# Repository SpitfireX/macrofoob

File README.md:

# macrofoob
A QMK-powered 5x5 macro pad with hot swap sockets and RGB underglow

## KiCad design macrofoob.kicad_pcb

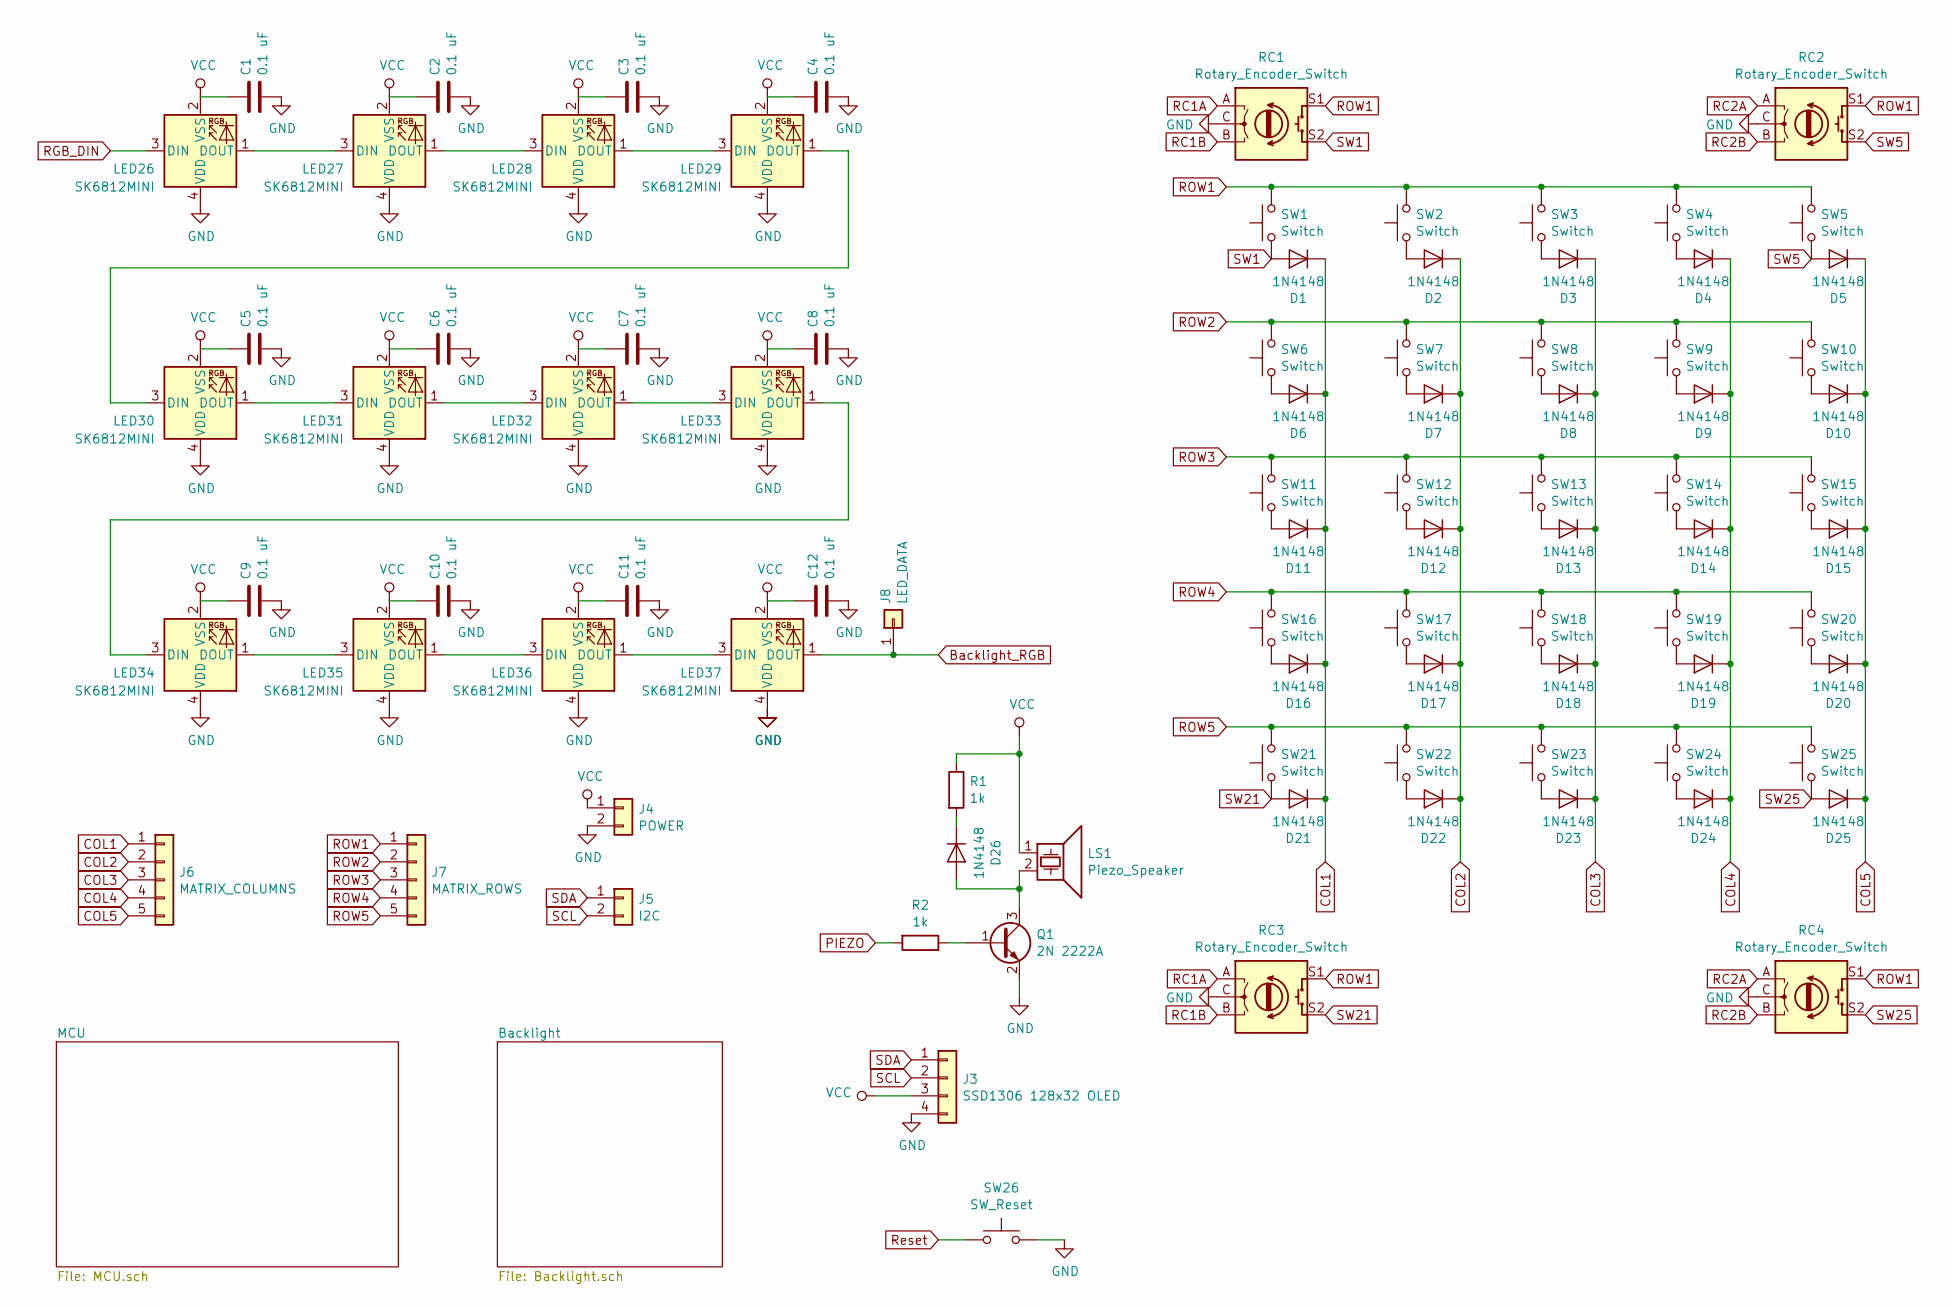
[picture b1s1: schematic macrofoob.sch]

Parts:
C1, C2, C3, C4, C5, C6, C7, C8, C9, C10, C11, C12: 0.1 uF; C_0805_2012Metric
D1, D2, D3, D4, D5, D6, D7, D8, D9, D10, D11, D12, D13, D14, D15, D16, D17, D18, D19, D20, D21, D22, D23, D24, D25, D26: 1N4148; D_MiniMELF
J3: SSD1306 128x32 OLED; PinHeader_1x04_P2.54mm_Vertical
J4: POWER; Generic_Pads_2mm_1x2
J5: I2C; Generic_Pads_2mm_1x2
J6: MATRIX_COLUMNS; Generic_Pads_2mm_1x5
J7: MATRIX_ROWS; Generic_Pads_2mm_1x5
J8: LED_DATA; Generic_Pads_2mm_1x1
LED26, LED27, LED28, LED29, LED30, LED31, LED32, LED33, LED34, LED35, LED36, LED37: SK6812MINI; LED_SK6812MINI_PLCC4_3.5x3.5mm_P1.75mm
LS1: Piezo_Speaker; PinHeader_1x02_P2.54mm_Vertical
Q1: 2N 2222A; SOT-23
R1, R2: 1k; R_0805_2012Metric
RC1, RC2, RC3, RC4: Rotary_Encoder_Switch; RotaryEncoder_Alps_EC11E-Switch_Vertical_H20mm_custom
SW1, SW2, SW3, SW4, SW5, SW6, SW7, SW8, SW9, SW10, SW11, SW12, SW13, SW14, SW15, SW16, SW17, SW18, SW19, SW20, SW21, SW22, SW23, SW24, SW25: Switch; Kailh_socket_optional
SW26: SW_Reset; SW_SPST_PTS810

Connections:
Backlight_RGB: J8.1, LED37.1 (DOUT); also elsewhere on the board
COL1: D1.1 (K), D6.1 (K), D11.1 (K), D16.1 (K), D21.1 (K), J6.1; also elsewhere on the board
COL2: D2.1 (K), D7.1 (K), D12.1 (K), D17.1 (K), D22.1 (K), J6.2; also elsewhere on the board
COL3: D3.1 (K), D8.1 (K), D13.1 (K), D18.1 (K), D23.1 (K), J6.3; also elsewhere on the board
COL4: D4.1 (K), D9.1 (K), D14.1 (K), D19.1 (K), D24.1 (K), J6.4; also elsewhere on the board
COL5: D5.1 (K), D10.1 (K), D15.1 (K), D20.1 (K), D25.1 (K), J6.5; also elsewhere on the board
GND: C1.2, C2.2, C3.2, C4.2, C5.2, C6.2, C7.2, C8.2, C9.2, C10.2, C11.2, C12.2, J3.4, J4.2, LED26.4 (VDD), LED27.4 (VDD), LED28.4 (VDD), LED29.4 (VDD), LED30.4 (VDD), LED31.4 (VDD), LED32.4 (VDD), LED33.4 (VDD), LED34.4 (VDD), LED35.4 (VDD), LED36.4 (VDD), LED37.4 (VDD), Q1.2 (E), RC1.C, RC2.C, RC3.C, RC4.C, SW26.2; also elsewhere on the board
unnamed: D2.2 (A), SW2.1
unnamed: D3.2 (A), SW3.1
unnamed: D4.2 (A), SW4.1
unnamed: D6.2 (A), SW6.1
unnamed: D7.2 (A), SW7.1
unnamed: D8.2 (A), SW8.1
unnamed: D9.2 (A), SW9.1
unnamed: D10.2 (A), SW10.1
unnamed: D11.2 (A), SW11.1
unnamed: D12.2 (A), SW12.1
unnamed: D13.2 (A), SW13.1
unnamed: D14.2 (A), SW14.1
unnamed: D15.2 (A), SW15.1
unnamed: D16.2 (A), SW16.1
unnamed: D17.2 (A), SW17.1
unnamed: D18.2 (A), SW18.1
unnamed: D19.2 (A), SW19.1
unnamed: D20.2 (A), SW20.1
unnamed: D22.2 (A), SW22.1
unnamed: D23.2 (A), SW23.1
unnamed: D24.2 (A), SW24.1
unnamed: D26.1 (K), R1.2
unnamed: D26.2 (A), LS1.2, Q1.3 (C)
unnamed: LED26.1 (DOUT), LED27.3 (DIN)
unnamed: LED27.1 (DOUT), LED28.3 (DIN)
unnamed: LED28.1 (DOUT), LED29.3 (DIN)
unnamed: LED29.1 (DOUT), LED30.3 (DIN)
unnamed: LED30.1 (DOUT), LED31.3 (DIN)
unnamed: LED31.1 (DOUT), LED32.3 (DIN)
unnamed: LED32.1 (DOUT), LED33.3 (DIN)
unnamed: LED33.1 (DOUT), LED34.3 (DIN)
unnamed: LED34.1 (DOUT), LED35.3 (DIN)
unnamed: LED35.1 (DOUT), LED36.3 (DIN)
unnamed: LED36.1 (DOUT), LED37.3 (DIN)
unnamed: Q1.1 (B), R2.1
PIEZO: R2.2; also elsewhere on the board
RC1A: RC1.A, RC3.A; also elsewhere on the board
RC1B: RC1.B, RC3.B; also elsewhere on the board
RC2A: RC2.A, RC4.A; also elsewhere on the board
RC2B: RC2.B, RC4.B; also elsewhere on the board
RGB_DIN: LED26.3 (DIN); also elsewhere on the board
ROW1: J7.1, RC1.S1, RC2.S1, RC3.S1, RC4.S1, SW1.2, SW2.2, SW3.2, SW4.2, SW5.2; also elsewhere on the board
ROW2: J7.2, SW6.2, SW7.2, SW8.2, SW9.2, SW10.2; also elsewhere on the board
ROW3: J7.3, SW11.2, SW12.2, SW13.2, SW14.2, SW15.2; also elsewhere on the board
ROW4: J7.4, SW16.2, SW17.2, SW18.2, SW19.2, SW20.2; also elsewhere on the board
ROW5: J7.5, SW21.2, SW22.2, SW23.2, SW24.2, SW25.2; also elsewhere on the board
Reset: SW26.1; also elsewhere on the board
SCL: J3.2, J5.2; also elsewhere on the board
SDA: J3.1, J5.1; also elsewhere on the board
SW1: D1.2 (A), RC1.S2, SW1.1
SW5: D5.2 (A), RC2.S2, SW5.1
SW21: D21.2 (A), RC3.S2, SW21.1
SW25: D25.2 (A), RC4.S2, SW25.1
VCC: C1.1, C2.1, C3.1, C4.1, C5.1, C6.1, C7.1, C8.1, C9.1, C10.1, C11.1, C12.1, J3.3, J4.1, LED26.2 (VSS), LED27.2 (VSS), LED28.2 (VSS), LED29.2 (VSS), LED30.2 (VSS), LED31.2 (VSS), LED32.2 (VSS), LED33.2 (VSS), LED34.2 (VSS), LED35.2 (VSS), LED36.2 (VSS), LED37.2 (VSS), LS1.1, R1.1; also elsewhere on the board

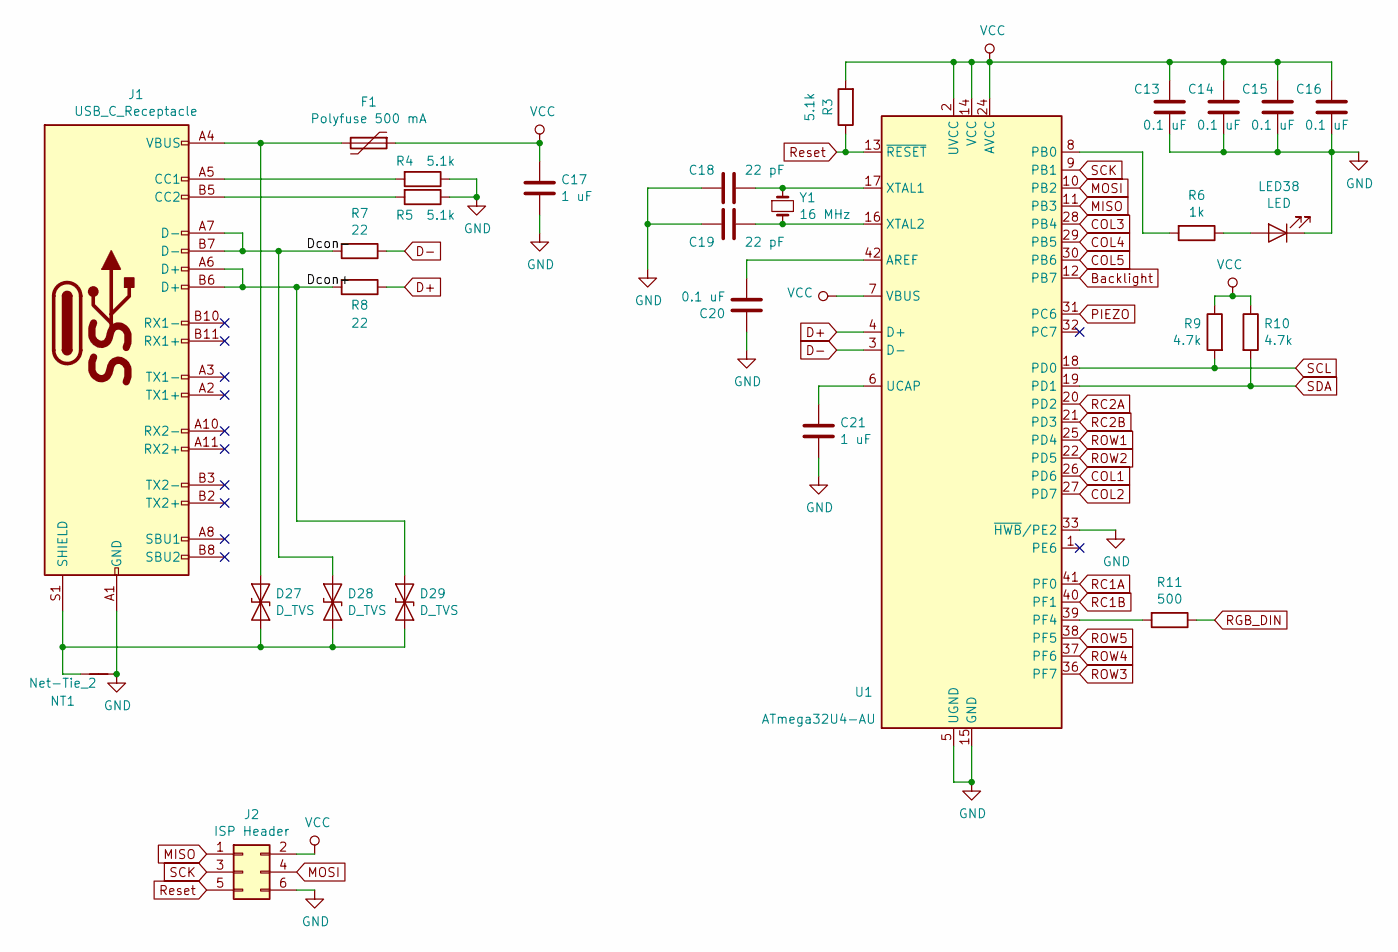
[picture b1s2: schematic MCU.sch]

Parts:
C13, C14, C15, C16, C20: 0.1 uF; C_0805_2012Metric
C17, C21: 1 uF; C_0805_2012Metric
C18, C19: 22 pF; C_0805_2012Metric
D27, D28, D29: D_TVS; D_SMA
F1: Polyfuse 500 mA; Fuse_1812_4532Metric
J1: USB_C_Receptacle; HRO-TYPE-C-31-M-12_kicad-pinout
J2: ISP Header; PinHeader_2x03_P2.54mm_Vertical
LED38: LED; LED_0805_2012Metric
NT1: Net-Tie_2; NetTie-2_SMD_Pad2.0mm
R3, R4, R5: 5.1k; R_0805_2012Metric
R6: 1k; R_0805_2012Metric
R7, R8: 22; R_0805_2012Metric
R9, R10: 4.7k; R_0805_2012Metric
R11: 500; R_0805_2012Metric
U1: ATmega32U4-AU; TQFP-44_10x10mm_P0.8mm
Y1: 16 MHz; R_1210_3225Metric

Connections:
/MCU/Dcon+: D29.1 (A1), J1.A6 (D+), J1.B6 (D+), R8.2
/MCU/Dcon-: D28.1 (A1), J1.A7 (D-), J1.B7 (D-), R7.2
Backlight: U1.12 (PB7); also elsewhere on the board
COL1: U1.26 (PD6); also elsewhere on the board
COL2: U1.27 (PD7); also elsewhere on the board
COL3: U1.28 (PB4); also elsewhere on the board
COL4: U1.29 (PB5); also elsewhere on the board
COL5: U1.30 (PB6); also elsewhere on the board
D+: R8.1, U1.4 (D+)
D-: R7.1, U1.3 (D-)
GND: C13.1, C14.1, C15.1, C16.1, C17.2, C18.2, C19.2, C20.1, C21.2, J1.A1 (GND), J1.A12 (GND), J1.B1 (GND), J1.B12 (GND), J2.6, LED38.1 (K), NT1.2, R4.1, R5.1, U1.5 (UGND), U1.15 (GND), U1.23 (GND), U1.33 (~HWB~/PE2), U1.35 (GND), U1.43 (GND); also elsewhere on the board
MISO: J2.1, U1.11 (PB3)
MOSI: J2.4, U1.10 (PB2)
unnamed: C18.1, U1.17 (XTAL1), Y1.1
unnamed: C19.1, U1.16 (XTAL2), Y1.2
unnamed: C20.2, U1.42 (AREF)
unnamed: C21.1, U1.6 (UCAP)
unnamed: D27.1 (A1), F1.2, J1.A4 (VBUS), J1.A9 (VBUS), J1.B4 (VBUS), J1.B9 (VBUS)
unnamed: D27.2 (A2), D28.2 (A2), D29.2 (A2), J1.S1 (SHIELD), NT1.1
unnamed: J1.A5 (CC1), R4.2
unnamed: J1.B5 (CC2), R5.2
unnamed: LED38.2 (A), R6.1
unnamed: R6.2, U1.8 (PB0)
unnamed: R11.2, U1.39 (PF4)
PIEZO: U1.31 (PC6); also elsewhere on the board
RC1A: U1.41 (PF0); also elsewhere on the board
RC1B: U1.40 (PF1); also elsewhere on the board
RC2A: U1.20 (PD2); also elsewhere on the board
RC2B: U1.21 (PD3); also elsewhere on the board
RGB_DIN: R11.1; also elsewhere on the board
ROW1: U1.25 (PD4); also elsewhere on the board
ROW2: U1.22 (PD5); also elsewhere on the board
ROW3: U1.36 (PF7); also elsewhere on the board
ROW4: U1.37 (PF6); also elsewhere on the board
ROW5: U1.38 (PF5); also elsewhere on the board
Reset: J2.5, R3.1, U1.13 (~RESET); also elsewhere on the board
SCK: J2.3, U1.9 (PB1)
SCL: R9.2, U1.18 (PD0); also elsewhere on the board
SDA: R10.2, U1.19 (PD1); also elsewhere on the board
VCC: C13.2, C14.2, C15.2, C16.2, C17.1, F1.1, J2.2, R3.2, R9.1, R10.1, U1.2 (UVCC), U1.7 (VBUS), U1.14 (VCC), U1.24 (AVCC), U1.34 (VCC), U1.44 (AVCC); also elsewhere on the board

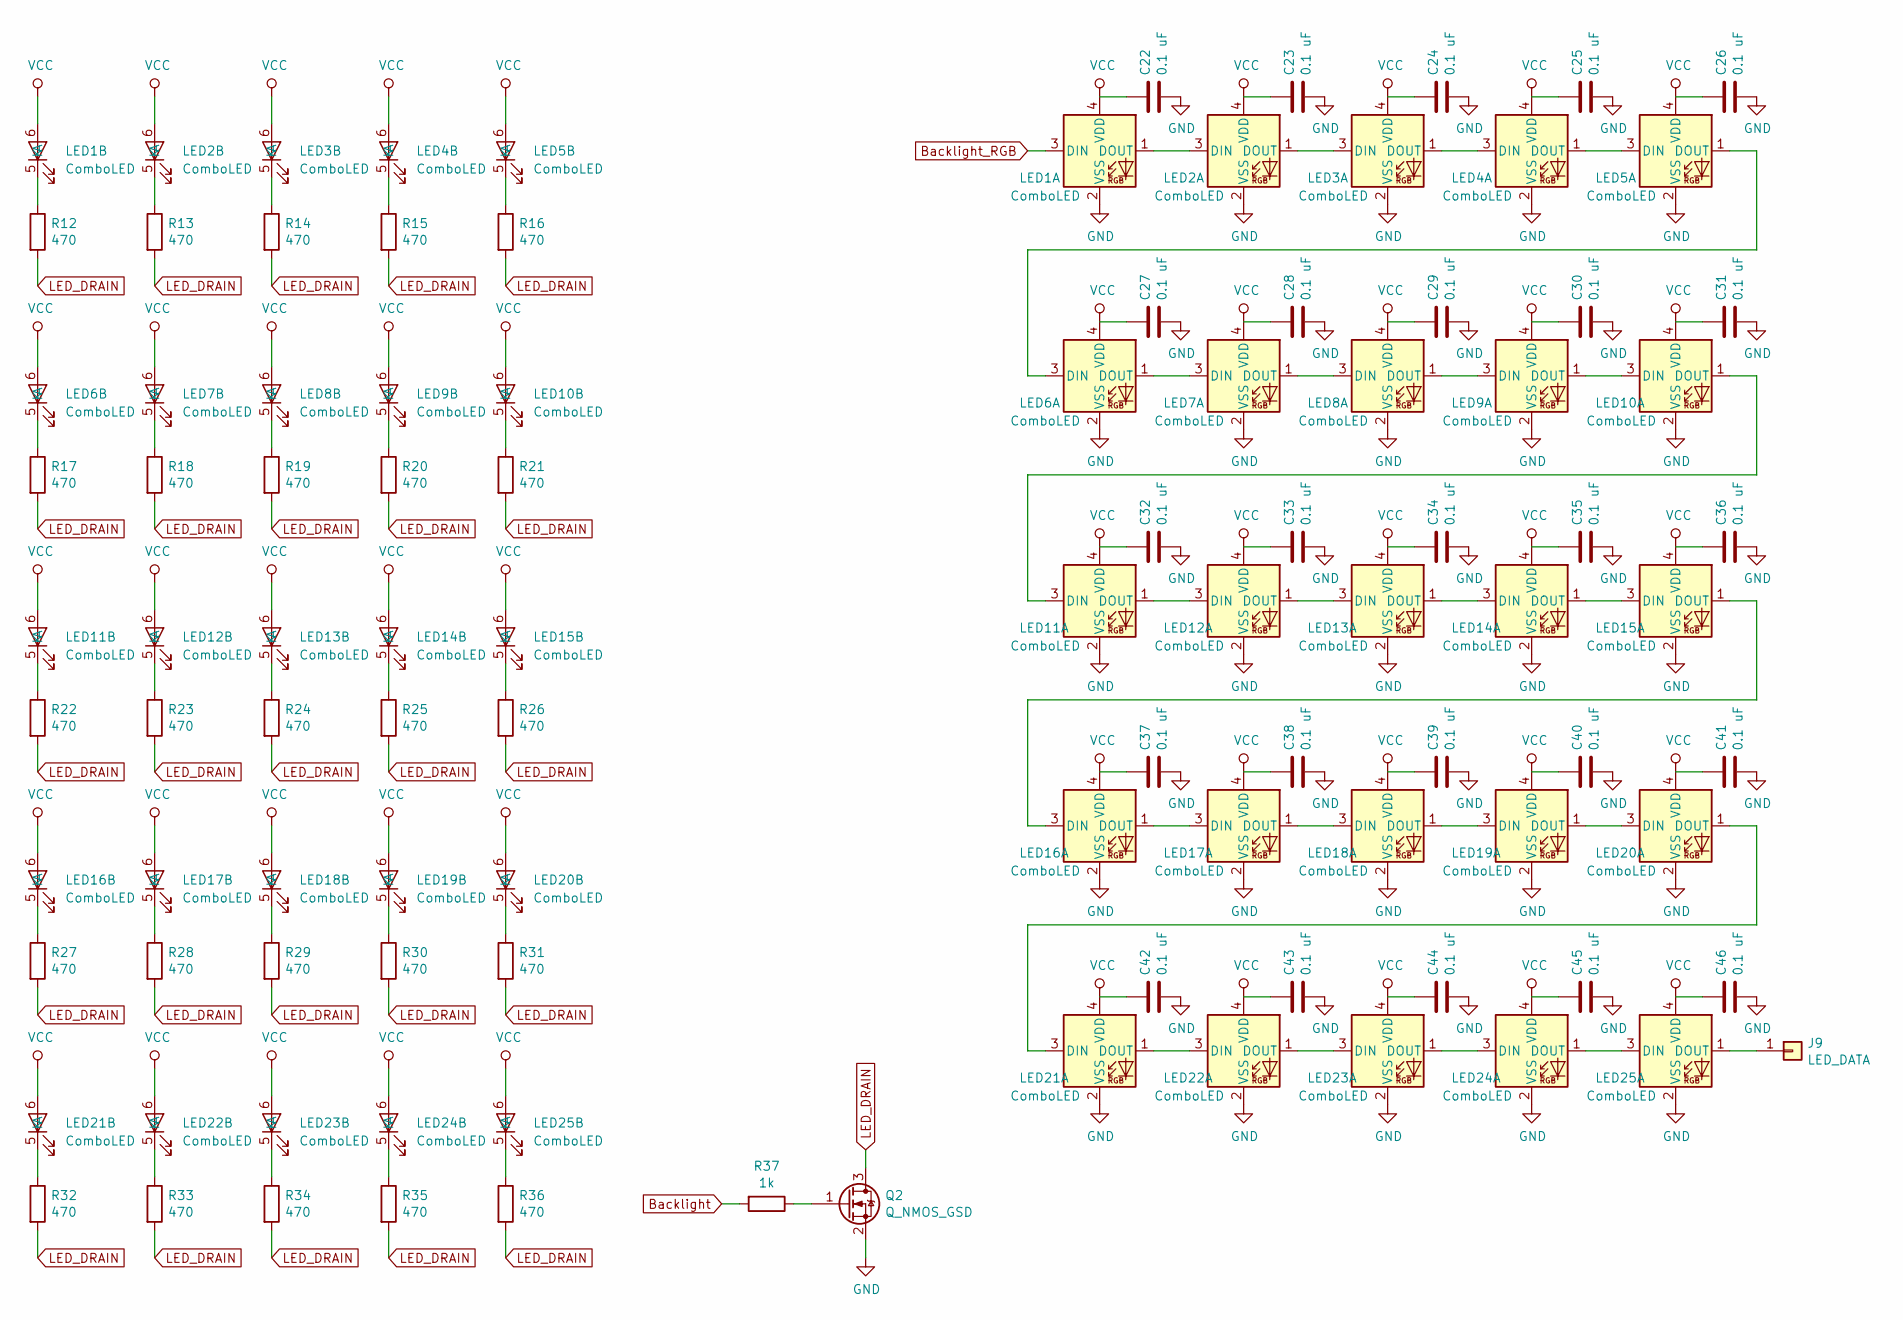
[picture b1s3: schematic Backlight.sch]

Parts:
C22, C23, C24, C25, C26, C27, C28, C29, C30, C31, C32, C33, C34, C35, C36, C37, C38, C39, C40, C41, C42, C43, C44, C45, C46: 0.1 uF; C_0805_2012Metric
J9: LED_DATA; Generic_Pads_2mm_1x1
LED1, LED2, LED3, LED4, LED5, LED6, LED7, LED8, LED9, LED10, LED11, LED12, LED13, LED14, LED15, LED16, LED17, LED18, LED19, LED20, LED21, LED22, LED23, LED24, LED25: ComboLED; LED_combined_SK6812MINI_0805
Q2: Q_NMOS_GSD; SOT-23
R12, R13, R14, R15, R16, R17, R18, R19, R20, R21, R22, R23, R24, R25, R26, R27, R28, R29, R30, R31, R32, R33, R34, R35, R36: 470; R_0805_2012Metric
R37: 1k; R_0805_2012Metric

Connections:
Backlight: R37.2; also elsewhere on the board
Backlight_RGB: LED1.3 (DIN); also elsewhere on the board
GND: C22.2, C23.2, C24.2, C25.2, C26.2, C27.2, C28.2, C29.2, C30.2, C31.2, C32.2, C33.2, C34.2, C35.2, C36.2, C37.2, C38.2, C39.2, C40.2, C41.2, C42.2, C43.2, C44.2, C45.2, C46.2, LED1.2 (VSS), LED2.2 (VSS), LED3.2 (VSS), LED4.2 (VSS), LED5.2 (VSS), LED6.2 (VSS), LED7.2 (VSS), LED8.2 (VSS), LED9.2 (VSS), LED10.2 (VSS), LED11.2 (VSS), LED12.2 (VSS), LED13.2 (VSS), LED14.2 (VSS), LED15.2 (VSS), LED16.2 (VSS), LED17.2 (VSS), LED18.2 (VSS), LED19.2 (VSS), LED20.2 (VSS), LED21.2 (VSS), LED22.2 (VSS), LED23.2 (VSS), LED24.2 (VSS), LED25.2 (VSS), Q2.2 (S); also elsewhere on the board
LED_DRAIN: Q2.3 (D), R12.2, R13.2, R14.2, R15.2, R16.2, R17.2, R18.2, R19.2, R20.2, R21.2, R22.2, R23.2, R24.2, R25.2, R26.2, R27.2, R28.2, R29.2, R30.2, R31.2, R32.2, R33.2, R34.2, R35.2, R36.2
unnamed: J9.1, LED25.1 (DOUT)
unnamed: LED1.1 (DOUT), LED2.3 (DIN)
unnamed: LED1.5 (K), R12.1
unnamed: LED2.1 (DOUT), LED3.3 (DIN)
unnamed: LED2.5 (K), R13.1
unnamed: LED3.1 (DOUT), LED4.3 (DIN)
unnamed: LED3.5 (K), R14.1
unnamed: LED4.1 (DOUT), LED5.3 (DIN)
unnamed: LED4.5 (K), R15.1
unnamed: LED5.1 (DOUT), LED6.3 (DIN)
unnamed: LED5.5 (K), R16.1
unnamed: LED6.1 (DOUT), LED7.3 (DIN)
unnamed: LED6.5 (K), R17.1
unnamed: LED7.1 (DOUT), LED8.3 (DIN)
unnamed: LED7.5 (K), R18.1
unnamed: LED8.1 (DOUT), LED9.3 (DIN)
unnamed: LED8.5 (K), R19.1
unnamed: LED9.5 (K), R20.1
unnamed: LED10.1 (DOUT), LED11.3 (DIN)
unnamed: LED9.1 (DOUT), LED10.3 (DIN)
unnamed: LED10.5 (K), R21.1
unnamed: LED11.1 (DOUT), LED12.3 (DIN)
unnamed: LED11.5 (K), R22.1
unnamed: LED12.1 (DOUT), LED13.3 (DIN)
unnamed: LED12.5 (K), R23.1
unnamed: LED13.1 (DOUT), LED14.3 (DIN)
unnamed: LED13.5 (K), R24.1
unnamed: LED14.1 (DOUT), LED15.3 (DIN)
unnamed: LED14.5 (K), R25.1
unnamed: LED15.1 (DOUT), LED16.3 (DIN)
unnamed: LED15.5 (K), R26.1
unnamed: LED16.1 (DOUT), LED17.3 (DIN)
unnamed: LED16.5 (K), R27.1
unnamed: LED17.1 (DOUT), LED18.3 (DIN)
unnamed: LED17.5 (K), R28.1
unnamed: LED18.1 (DOUT), LED19.3 (DIN)
unnamed: LED18.5 (K), R29.1
unnamed: LED19.1 (DOUT), LED20.3 (DIN)
unnamed: LED19.5 (K), R30.1
unnamed: LED20.1 (DOUT), LED21.3 (DIN)
unnamed: LED20.5 (K), R31.1
unnamed: LED21.1 (DOUT), LED22.3 (DIN)
unnamed: LED21.5 (K), R32.1
unnamed: LED22.1 (DOUT), LED23.3 (DIN)
unnamed: LED22.5 (K), R33.1
unnamed: LED23.1 (DOUT), LED24.3 (DIN)
unnamed: LED23.5 (K), R34.1
unnamed: LED24.1 (DOUT), LED25.3 (DIN)
unnamed: LED24.5 (K), R35.1
unnamed: LED25.5 (K), R36.1
unnamed: Q2.1 (G), R37.1
VCC: C22.1, C23.1, C24.1, C25.1, C26.1, C27.1, C28.1, C29.1, C30.1, C31.1, C32.1, C33.1, C34.1, C35.1, C36.1, C37.1, C38.1, C39.1, C40.1, C41.1, C42.1, C43.1, C44.1, C45.1, C46.1, LED1.4 (VDD), LED1.6 (A), LED2.4 (VDD), LED2.6 (A), LED3.4 (VDD), LED3.6 (A), LED4.4 (VDD), LED4.6 (A), LED5.4 (VDD), LED5.6 (A), LED6.4 (VDD), LED6.6 (A), LED7.4 (VDD), LED7.6 (A), LED8.4 (VDD), LED8.6 (A), LED9.4 (VDD), LED9.6 (A), LED10.4 (VDD), LED10.6 (A), LED11.4 (VDD), LED11.6 (A), LED12.4 (VDD), LED12.6 (A), LED13.4 (VDD), LED13.6 (A), LED14.4 (VDD), LED14.6 (A), LED15.4 (VDD), LED15.6 (A), LED16.4 (VDD), LED16.6 (A), LED17.4 (VDD), LED17.6 (A), LED18.4 (VDD), LED18.6 (A), LED19.4 (VDD), LED19.6 (A), LED20.4 (VDD), LED20.6 (A), LED21.4 (VDD), LED21.6 (A), LED22.4 (VDD), LED22.6 (A), LED23.4 (VDD), LED23.6 (A), LED24.4 (VDD), LED24.6 (A), LED25.4 (VDD), LED25.6 (A); also elsewhere on the board

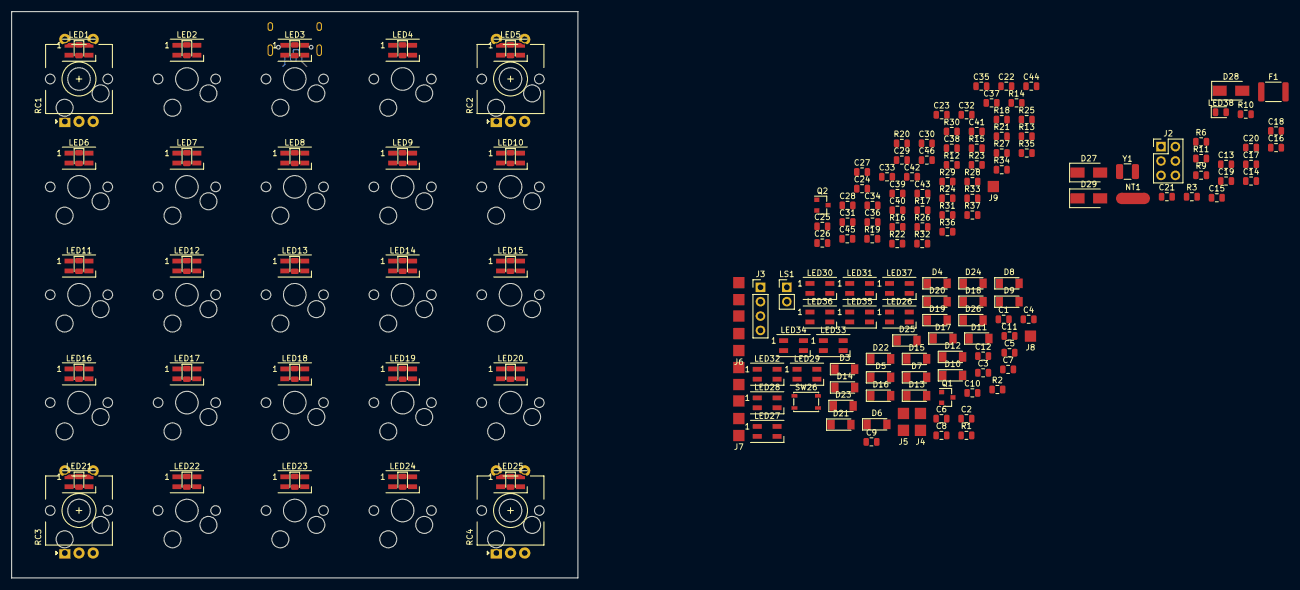
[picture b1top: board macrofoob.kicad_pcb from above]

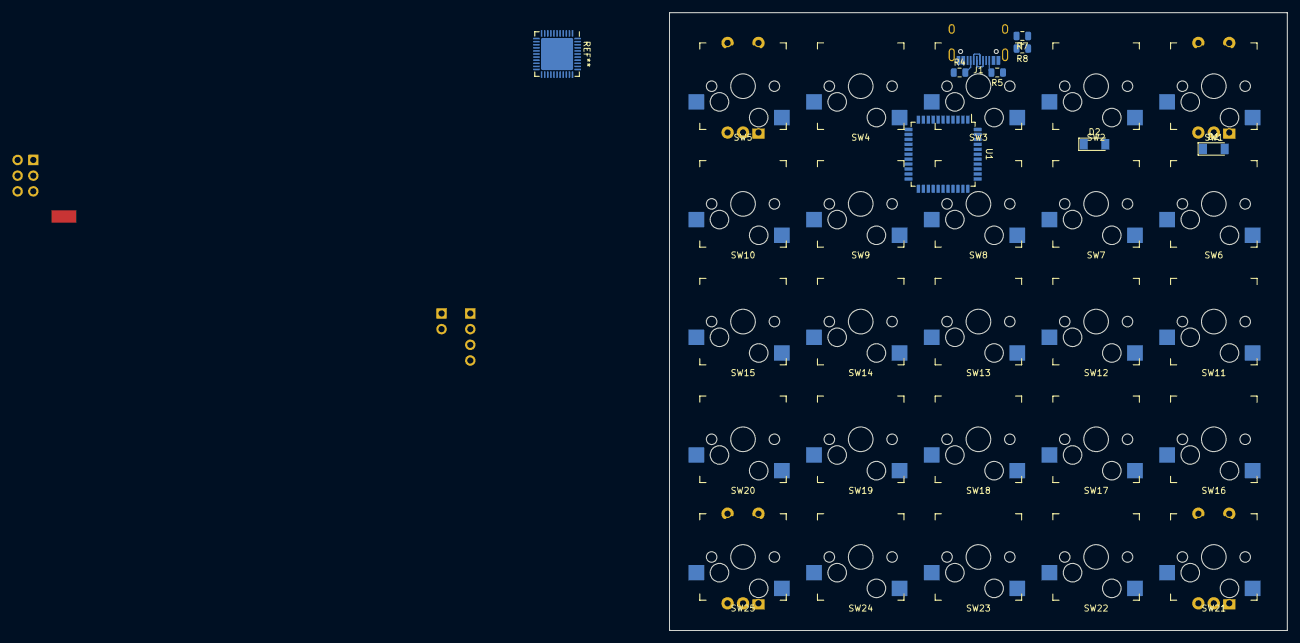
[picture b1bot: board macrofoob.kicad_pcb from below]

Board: 2 copper layers, 100.0 x 100.0 mm, 196 parts (8 on the bottom side), 132 nets.

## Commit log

2019-08-31 initial commit with full schematic
2019-08-31 improved piezo circuit
2019-08-31 cleanup and added oled header
2019-08-31 cleanup and added oled header 2
2019-09-01 added oled header
2019-09-01 first pcb layout and new footprints
2019-09-04 updated gitignore to get rid of fp-info-cache
2019-09-04 added Keebio-Parts.pretty submodule
2019-09-07 replaced the pro micro with a standalone atmega32u4 implementation
2019-09-07 added new TQFP-44 footprint with shorter pads
2019-09-07 added backlight to schematic and board setup to PCB
2019-09-08 added new generic SMD pad footprints and footprint associations
2019-09-08 new custom footprints for clearance of rotary encoder and led
2019-09-08 added new symbol and footprint for combined LED footprint
2019-09-08 added footprint association for new combined LED symbol
2019-09-08 updated schematic with more backlight options
2019-09-08 added Type-C.pretty submodule
2019-09-08 added customized HRO-TYPE-C footprint
2019-09-08 fixed error in the combined LED footprint so symbols arent interchangeable anymore
2019-09-08 new component annotations
2019-09-09 fixed power flags
2019-09-09 initial pcb layout and schematic optimizations
